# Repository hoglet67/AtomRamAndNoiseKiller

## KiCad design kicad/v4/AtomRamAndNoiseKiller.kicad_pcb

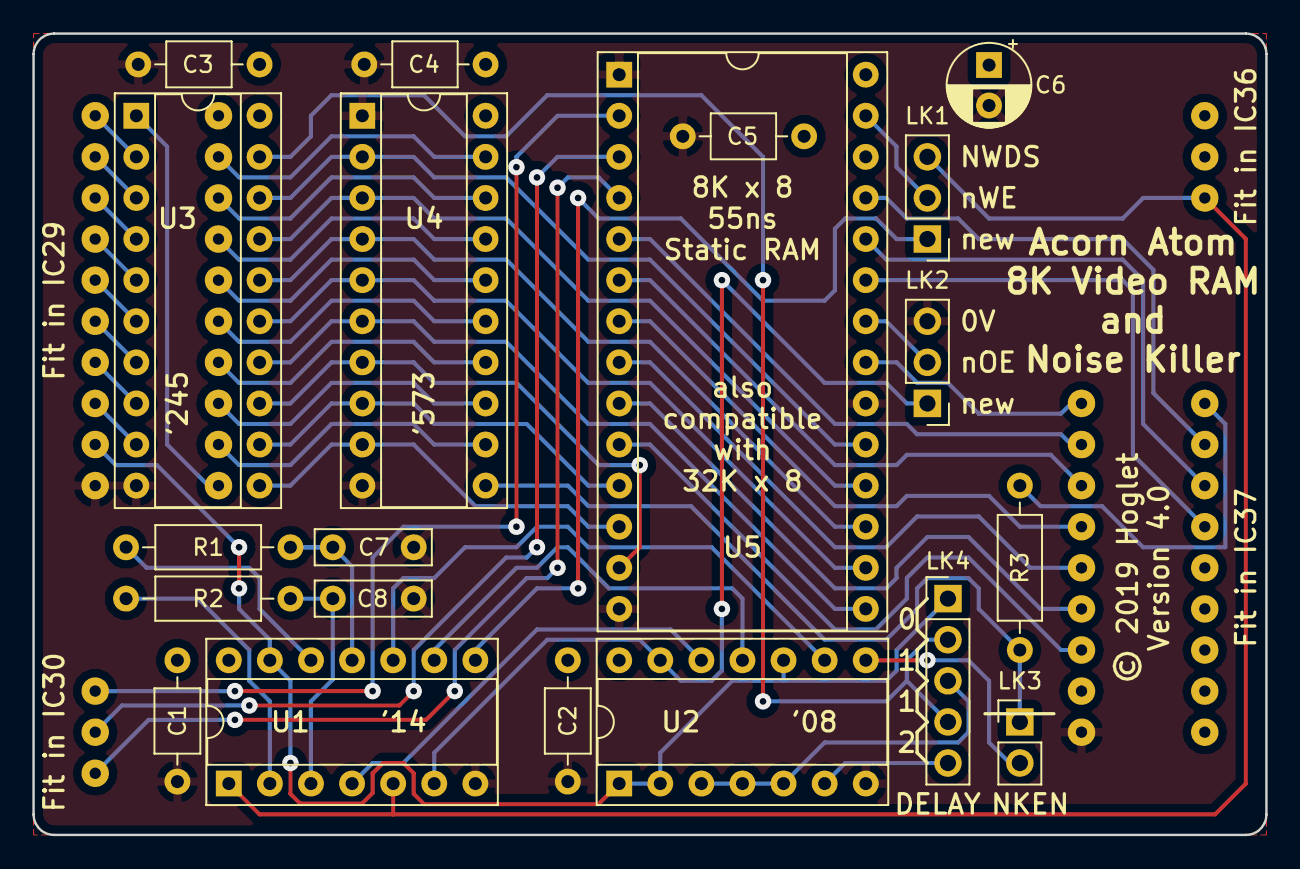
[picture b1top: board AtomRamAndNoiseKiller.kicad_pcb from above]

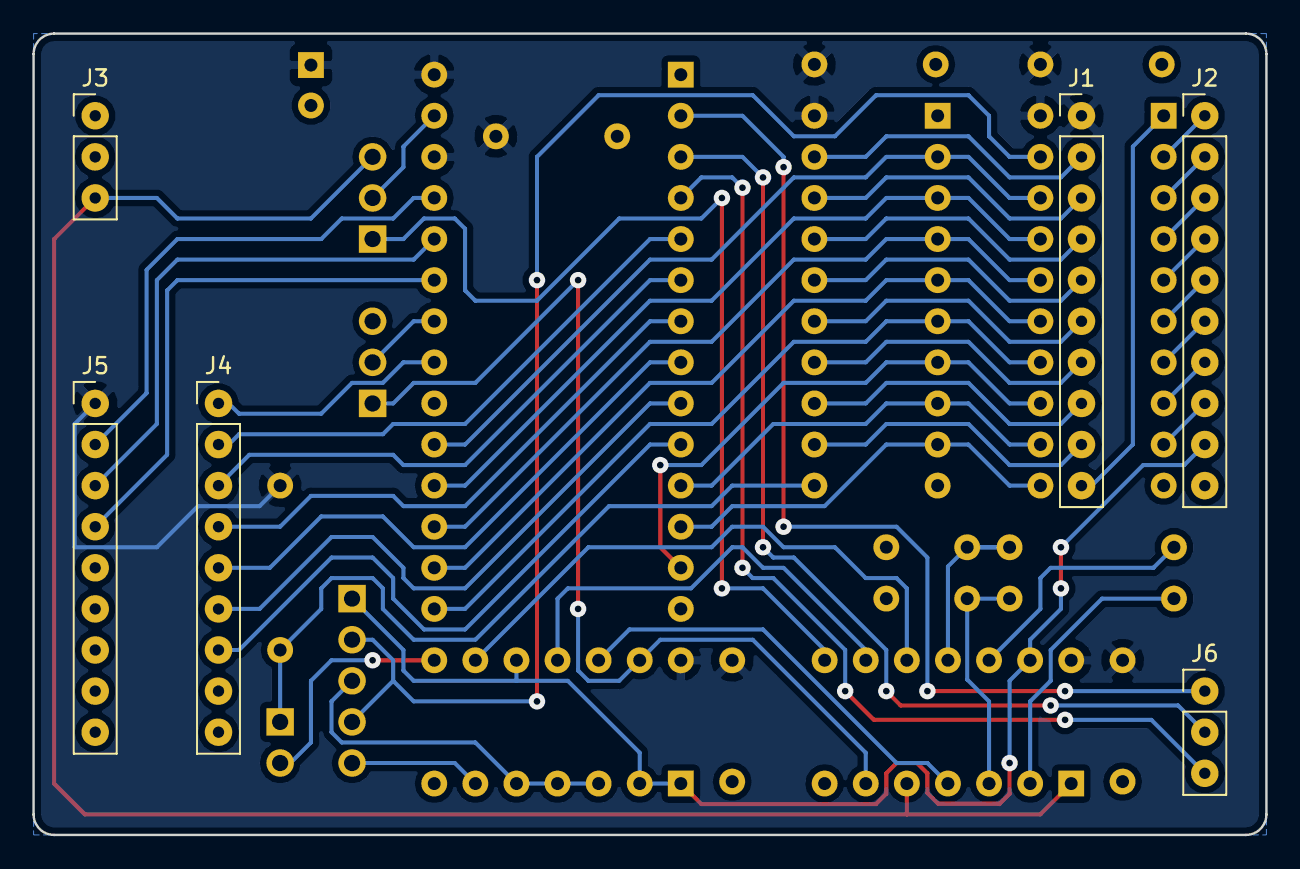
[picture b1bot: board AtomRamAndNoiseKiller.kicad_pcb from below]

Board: 2 copper layers, 76.2 x 49.5 mm, 26 parts (6 on the bottom side), 58 nets.

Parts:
C1, C2, C3, C4, C5: 100n; C_Axial_L3.8mm_D2.6mm_P7.50mm_Horizontal
C6: 10u; CP_Radial_D5.0mm_P2.50mm
C7, C8: 100p; C_Rect_L7.0mm_W2.0mm_P5.00mm
J1, J2: Conn_01x10; FinePinHeader_1x10_P2.54mm_Vertical
J3, J6: Conn_01x03; FinePinHeader_1x03_P2.54mm_Vertical
J4, J5: Conn_01x09; FinePinHeader_1x09_P2.54mm_Vertical
LK1, LK2: Conn_01x03; PinHeader_1x03_P2.54mm_Vertical
LK3: Conn_01x02; PinHeader_1x02_P2.54mm_Vertical
LK4: Conn_01x05; PinHeader_1x05_P2.54mm_Vertical
R1: 270R; R_Axial_DIN0207_L6.3mm_D2.5mm_P10.16mm_Horizontal
R2: 1K0; R_Axial_DIN0207_L6.3mm_D2.5mm_P10.16mm_Horizontal
R3: 10K; R_Axial_DIN0207_L6.3mm_D2.5mm_P10.16mm_Horizontal
U1: 74HCT14; DIP-14_W7.62mm_Socket
U2: 74HCT08; DIP-14_W7.62mm_Socket
U3: 74HCT245; DIP-20_W7.62mm_Socket
U4: 74HCT573; DIP-20_W7.62mm_Socket
U5: 8Kx8 SRAM; DIP-28_W15.24mm_Socket

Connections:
/A0: J4.5, U5.8
/A1: J4.6, U5.9
/A2: J4.7, U5.10
/A3: J4.4, U5.7
/A4: J4.3, U5.6
/A5: J4.2, U5.5
/A6: J4.1, U5.21
/A7: J5.2, U5.25
/A8: J5.3, U5.24
/A9: J5.4, U5.23
/A10: J6.1, U5.2
/A11: J6.2, U5.3
/A12: J6.3, U5.4
/LOAD: LK3.1, R3.2, U4.11
/NDRS: J1.10, U3.1
/NVDG: J2.9, LK4.1, U1.13, U2.1, U2.2, U2.10
/NWE: J3.3, LK1.3, U1.1, U1.5
/PD0: J2.1, U3.2
/PD1: J2.2, U3.3
/PD2: J2.3, U3.4
/PD3: J2.4, U3.5
/PD4: J2.5, U3.6
/PD5: J2.6, U3.7
/PD6: J2.7, U3.8
/PD7: J2.8, U3.9
/RAMNOE: LK2.2, U5.22
/RAMNWE: LK1.2, U5.27
/RD0: U3.18, U4.2, U5.19
/RD1: U3.17, U4.3, U5.18
/RD2: U3.16, U4.4, U5.17
/RD3: U3.15, U4.5, U5.16
/RD4: U3.14, U4.6, U5.15
/RD5: U3.13, U4.7, U5.13
/RD6: U3.12, U4.8, U5.11
/RD7: U3.11, U4.9, U5.12
/VD0: J1.2, U4.19
/VD1: J1.3, U4.18
/VD2: J1.4, U4.17
/VD3: J1.5, U4.16
/VD4: J1.6, U4.15
/VD5: J1.7, U4.14
/VD6: J1.8, U4.13
/VD7: J1.9, U4.12
GND: C1.2, C2.2, C3.2, C4.2, C5.2, C6.2, C7.2, C8.2, J2.10, J4.9, LK2.3, U1.7, U2.7, U3.10, U4.1, U4.10, U5.1, U5.14, U5.20
unnamed: C7.1, R1.2, U1.11
unnamed: C8.1, R2.2, U1.3
unnamed: LK1.1, U1.8
unnamed: LK2.1, U1.6, U2.13
unnamed: LK3.2, U2.8
unnamed: LK4.2, LK4.4, U3.19
unnamed: LK4.3, U2.3, U2.4, U2.5
unnamed: LK4.5, U2.6
unnamed: R1.1, U1.12
unnamed: R2.1, U1.2
unnamed: U1.4, U2.12
unnamed: U1.9, U2.11
unnamed: U1.10, U2.9
VCC: C1.1, C2.1, C3.1, C4.1, C5.1, C6.1, J1.1, J5.1, R3.1, U1.14, U2.14, U3.20, U4.20, U5.26, U5.28

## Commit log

2019-04-14 KiCad: Initial work
2019-04-14 KiCad: Fully routed
2019-04-14 More work
2019-04-14 Almost finished
2019-04-14 Switched to HCT parts (cheaper)
2019-04-14 Added PDF Schematic
2019-04-14 Added manifacturing files
2019-04-16 V2 of the schamtics and PCB
2019-04-16 Final tweaks
2019-04-16 Moved J7 in a tad
2019-04-16 Added manufacturing files
2019-04-22 V3 of the schematics and PCB
2019-05-03 Swapped NRDS and VDG on header
2019-05-04 Updates PDF version of v3 schematic
2019-05-14 Updated R2 from 270R to 1K0
2019-07-25 v4.0: Fix incompatibility with 8Kx8 SRAM (connect pin 26 to VCC, not GND
2019-08-10 Final v2 schematics and bodge

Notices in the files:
kicad/v4/AtomRamAndNoiseKiller.kicad_pcb:
© 2019 Hoglet
